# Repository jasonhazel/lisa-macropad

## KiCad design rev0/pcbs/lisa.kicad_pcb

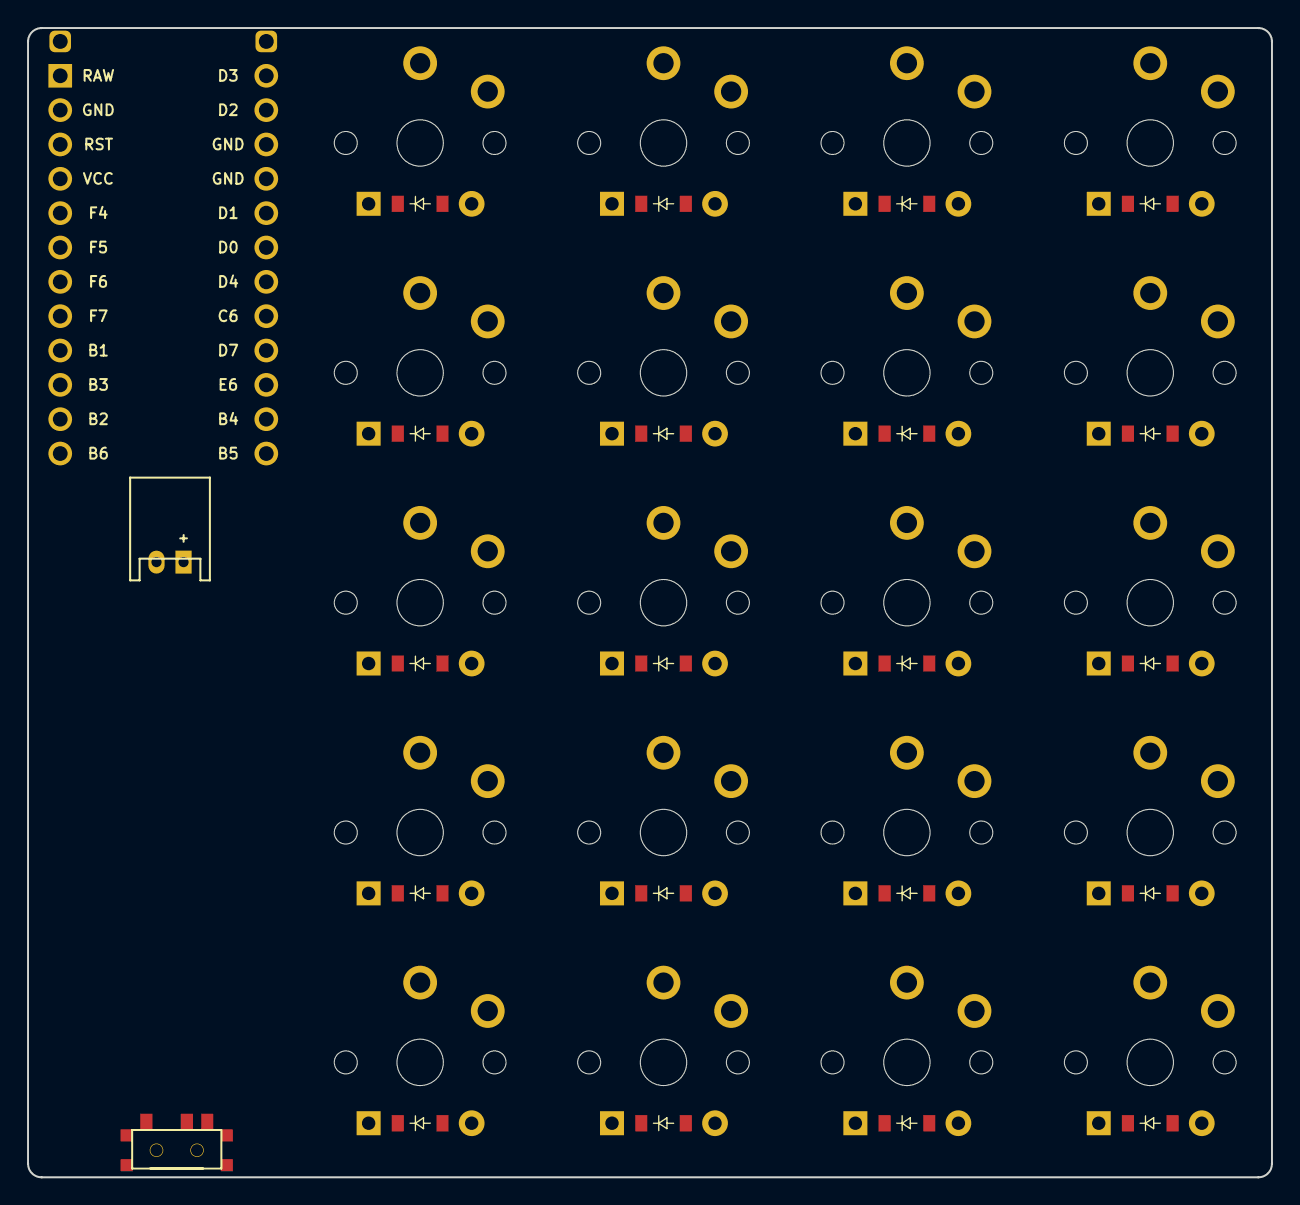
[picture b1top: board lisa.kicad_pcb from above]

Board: 2 copper layers, 92.0 x 85.0 mm, 43 parts (0 on the bottom side), 32 nets, no tracks yet.

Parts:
D1, D2, D3, D4, D5, D6, D7, D8, D9, D10, D11, D12, D13, D14, D15, D16, D17, D18, D19, D20: ComboDiode
JST1: JST_PH_S2B-PH-K_02x2.00mm_Angled
MCU1: ProMicro
S1, S2, S3, S4, S5, S6, S7, S8, S9, S10, S11, S12, S13, S14, S15, S16, S17, S18, S19, S20: PG1350
T1: SPDT_C128955

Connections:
B4: D1.1, D1.2, D6.1, D6.2, D11.1, D11.2, D16.1, D16.2, MCU1.23
BAT: JST1.1, T1.2
C6: MCU1.20, S11.2, S12.2, S13.2, S14.2, S15.2
D0: D2.1, D2.2, D7.1, D7.2, D12.1, D12.2, D17.1, D17.2, MCU1.18
D1: D3.1, D3.2, D8.1, D8.2, D13.1, D13.2, D18.1, D18.2, MCU1.17
D2: D4.1, D4.2, D9.1, D9.2, D14.1, D14.2, D19.1, D19.2, MCU1.14
D3: D5.1, D5.2, D10.1, D10.2, D15.1, D15.2, D20.1, D20.2, MCU1.13
D4: MCU1.19, S16.2, S17.2, S18.2, S19.2, S20.2
D7: MCU1.21, S6.2, S7.2, S8.2, S9.2, S10.2
E6: MCU1.22, S1.2, S2.2, S3.2, S4.2, S5.2
GND: JST1.2, MCU1.2, MCU1.15, MCU1.16
RAW: MCU1.1, T1.1
four_fifth: D20.1, D20.2, S20.1
four_first: D16.1, D16.2, S16.1
four_fourth: D19.1, D19.2, S19.1
four_second: D17.1, D17.2, S17.1
four_third: D18.1, D18.2, S18.1
one_fifth: D5.1, D5.2, S5.1
one_first: D1.1, D1.2, S1.1
one_fourth: D4.1, D4.2, S4.1
one_second: D2.1, D2.2, S2.1
one_third: D3.1, D3.2, S3.1
three_fifth: D15.1, D15.2, S15.1
three_first: D11.1, D11.2, S11.1
three_fourth: D14.1, D14.2, S14.1
three_second: D12.1, D12.2, S12.1
three_third: D13.1, D13.2, S13.1
two_fifth: D10.1, D10.2, S10.1
two_first: D6.1, D6.2, S6.1
two_fourth: D9.1, D9.2, S9.1
two_second: D7.1, D7.2, S7.1
two_third: D8.1, D8.2, S8.1

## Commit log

2022-11-22 init
